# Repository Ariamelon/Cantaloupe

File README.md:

# Cantaloupe
~60% 60-key ZMK-compatible wireless split ergonomic keyboard.

## Disclaimer
This keyboard is licensed under CERN-OHL-S-2.0. The layout is based on the [Ergodash](https://github.com/omkbd/ErgoDash) layout with the inner-most keys removed and an improved thumb cluster. The layout was only used as a reference, nothing was copied and the board is a completely new design.

## Key Features
* Ergonomic split 30-key vertically staggered layout with thumb cluster, pinky stagger and arrow keys.
* [VIK](https://github.com/sadekbaroudi/vik) module support.
* On-board nRF52840 BLE 5.3 MCU.
* nPM1300 PMIC for power management.
* Battery shipping mode switch while allowing for charging when plugged in.
* 702050 700mAh battery with built-in NTC for temperature protection.
* SWD Tag-Connect header for debugging purposes.
* USB-C input with full ESD protection.
* MX, Kailh Choc V1/V2 and Gateron KS-27/KS-33 hotswap support.
* Gasket-mount case with adjustable tent (?).

## Changelog
* 22/10/2024: License updated to CERN-OHL-S-2.0.
* 16/10/2024: Cantaloupe V3.0 name changed to CantaloupeBT V1.0 ('BT-V1' branch). Key features updated. Design will be reworked in the coming days!
* 24/08/2023: Finished routing. Consolidated all libraries into [Ariamelon's Kicad Master Library](https://github.com/Ariamelon/Ariamelon-Kicad-Master-Library). Added PCM12 switch connected to nPM1300 GPIO. Rearranged components and rerouted. 
* 23/08/2023: Changed MCU to nRF52840. Added nPM1300 PMIC for power management. Replaced SSD1351 display with Nice!View. Added Kailh Choc V1/V2 and Gateron KS-27/KS-33 support. 
* 08/08/2023: Removed Ogen footprint, and future VIK support is planned. Rerouted board following latest Honeydew revision. WIP support for the USB2541 is added, but it's very tentative and not yet complete. Added CX70M-24P1 footprint.
* 25/03/2023: Routing complete. Footprint added for the [Ogen](https://github.com/Ariamelon/Ogen/), allowing for a trackball or trackpad to be used.
* 19/03/2023: Initial V3.0 version committed (still in progress). Board has been completely reworked (again) and will be another completely new design, based on the [Honeydew](https://github.com/Ariamelon/Honeydew/). Added CC BY 4.0 license.
* 30/05/2022: Changed XC6206P332MR-G to XC6220B331MR-G for more power output. Changed fuse to 1A. Fixed library links. Changed AO6802 back to two AO3400s. Moved reset circuit downwards and extra pin header upwards for better routing. Updated BOM.
* 28/05/2022: Added another 10u filtering cap. Rerouted power track. Changed pin assignments. Changed values of VBUS detect to use already existing values on the board.
* 26/05/2022: Fixed mistakes with bottom cases. Added piece which is meant to mate with the button, allowing the reset to be pressed without needing a screwdriver. Update to USB port name and footprint (no functional change). Updated pin assignments. Rerouted board.
* 24/05/2022: Changed the matrix diodes to dual MMBD4148ACC diodes. Swapped ROW1 and COL0 pins. Fixed minor issue with case models. Updated BOM. Added LCSC part names to all parts on schematic.
* 23/05/2022: Updated trackpad plate models. Fixed OLED silk. 
* 22/05/2022: Added footprints for SPI FRAM/EEPROM and flash memory. Added breakout header to expose some unused pins. Fixed 3D models for plate pot. Updated 3D model for the EC11. Changed the two AO3400s to a AO6802 dual NMOS. Replaced switch with a more durable version that's the same size while keeping the footprint compatible with the previous switch. Updated BOM.
* 21/05/2022: Revised schematic. Switched trackpad to SPI interface and moved header. Moved location of OLED screen and changed footprint. Changed indicator LED to a small RGB one, and added an RGB header. Moved USB ports and reset button. Much better revised cases. Slightly increased horizontal size to fully accommodate the Cirque TM35035. Added lots of 3D models for all the footprints. Removed V1 as that was no longer being updated.
* 15/05/2022: V2.1 version updates. Removed silkscreen jumper guides, pimoroni trackball header and plate for trackpad. Updated BOM.
* 14/05/2022: Added silkscreen jumper guides. Connected indicator LED to spare GPIO. Updated images. Added optional I2C resistors. New logo. New plate CAD files for potentiometer, trackball and trackpad options. Added header for Cirque trackpad. Cleaned up footprint library.
* 13/05/2022: Updated firmware. Added custom graphic to OLED display. Updated 3DP case and BOM. Removed CNC case. Fixed error with silkscreen. Added silkscreen jumper guides.
* 15/02/2022: Revised 3DP and CNC case designs.
* 13/02/2022: Added tentative designs for CNC and 3D printed cases. 
* 11/02/2022: Clean up of design. New images. Added gerbers and files for FR4 plates.
* 9/02/2022: Changed pin assignments so B2 isn't used. Added pull-up for RX pin and pull-down for B2 pin so the keyboard can properly load into the bootloader. Changed reset circuit so it actually works. Removed USB series resistors. Removed non-functional JTAG pins. Changed SRV05-04 to SRV0504. Thanks to sigprof and MasterSpoon from the QMK discord server for the help!
* 8/02/2022: Removed holes in middle of PCB. Added top and bottom plate DXF files, as well as a tentative STEP file for a CNC case. 
* 25/01/2022: Did some rerouting, increased clearances and via size.
* 21/01/2022: Changed CPU to STM32F401CCU6 (lets me steal them from Black Pill boards). Added plate and base gerber files. Changed BOM to reflect changes.
* 20/01/2022: Cleaned up read-me. Rearranged location of mounting holes and changed size of holes. Rerouted some traces. Cleaned up silkscreen. Added DXF files for plate and base. Changed images. Added BOM.
* 19/01/2022: New V2.0 version. On-board ARM STM32F303 processor, kailh hot-swap, ESD protection, 0.96" OLED, trackball and rotary encoder. 100% reversible design which means only a single board is needed for both sides. Plenty of design cues taken from the YAEMK. Pinky stagger added.
* 6/12/2021: Updated to V1.5. Added the option for OLED again. Removed Alps support. Improved switch footprints. Removed 2u support and moved rotary encoder positions. Deleted 61st and 62nd keyswitches - now has exactly 30 switches per side. Changed USB C interconnect back to TRRS and moved position.
* 1/10/2021: Added SMK support again (I'm indecisive).
* 20/07/2021: Updated to V1.4. Removed OLED support, as I don't actually care about OLED and haven't been using it with the previous prototype for a while.
* 17/05/2021: Fixed BOM and added proper OLED support.
* 2/12/2020: Changed orientation of 1u switches in thumb cluster. Updated plate to add 2u support.
* 1/12/2020: Changed OLED compatibility to 0.96" OLED. Removed Crenshaw compatibility. Removed large cutout in plate for pro micro and Crenshaw, added smaller cutout just showing screen of 0.96" OLED.
* 29/11/2020: Updated to V1.3. Added 2u switch locations in outer bottom corners and thumb cluster. Slightly increased size to allow for high-profile case options. Changed mounting holes on PCB to pass-through holes to allow for direct top and bottom plate mounting. Removed SMK switch support. Updated plate to add Alps compatibility.
* 14/11/2020: Changed USB C connector to normal from mid-mount.
* 11/11/2020: Updated to V1.2. Switch footprints changed to solder holes, compatible with MX, Alps and SMK switches. 5-way switch removed. Pro Micros flipped, facing downward, to reduce overall thickness of keyboard. Diode footprints changed to allow use of both TH and SMD (SOD-123(F) and glass DO-35) diodes.
* 7/11/2020: Fixed position of RHS screw hole and wiring of rotary encoder switch, added QMK firmware.
* 28/10/2020: Better photo, reorganized footprints, minor fixes to circuit.
* 25/10/2020: Added back 5-way switch. Removed SMK support. New renders.
* 24/10/2020: Updated to V1.1. Slightly increased stagger and different PCB shape based on the [Galia](https://github.com/Ariamelon/Galia), removed snap-away interconnect section of PCB, added ICSP header. Moved location of images folder.
* 28/09/2020: Added case files.
* 27/09/2020: Initial commit.

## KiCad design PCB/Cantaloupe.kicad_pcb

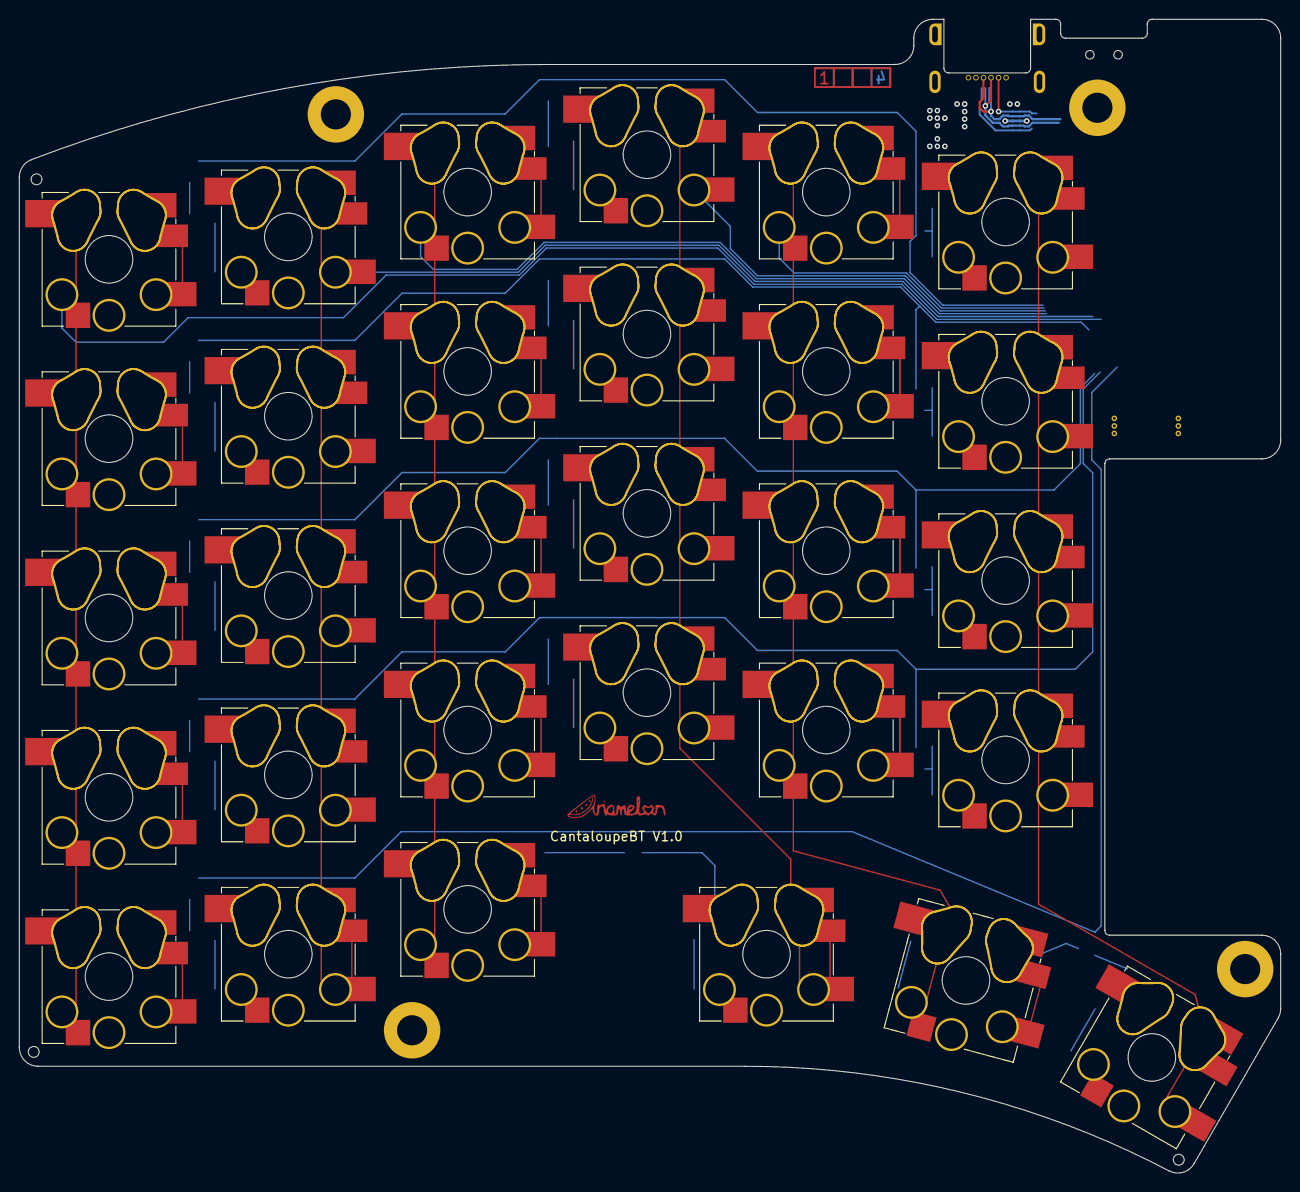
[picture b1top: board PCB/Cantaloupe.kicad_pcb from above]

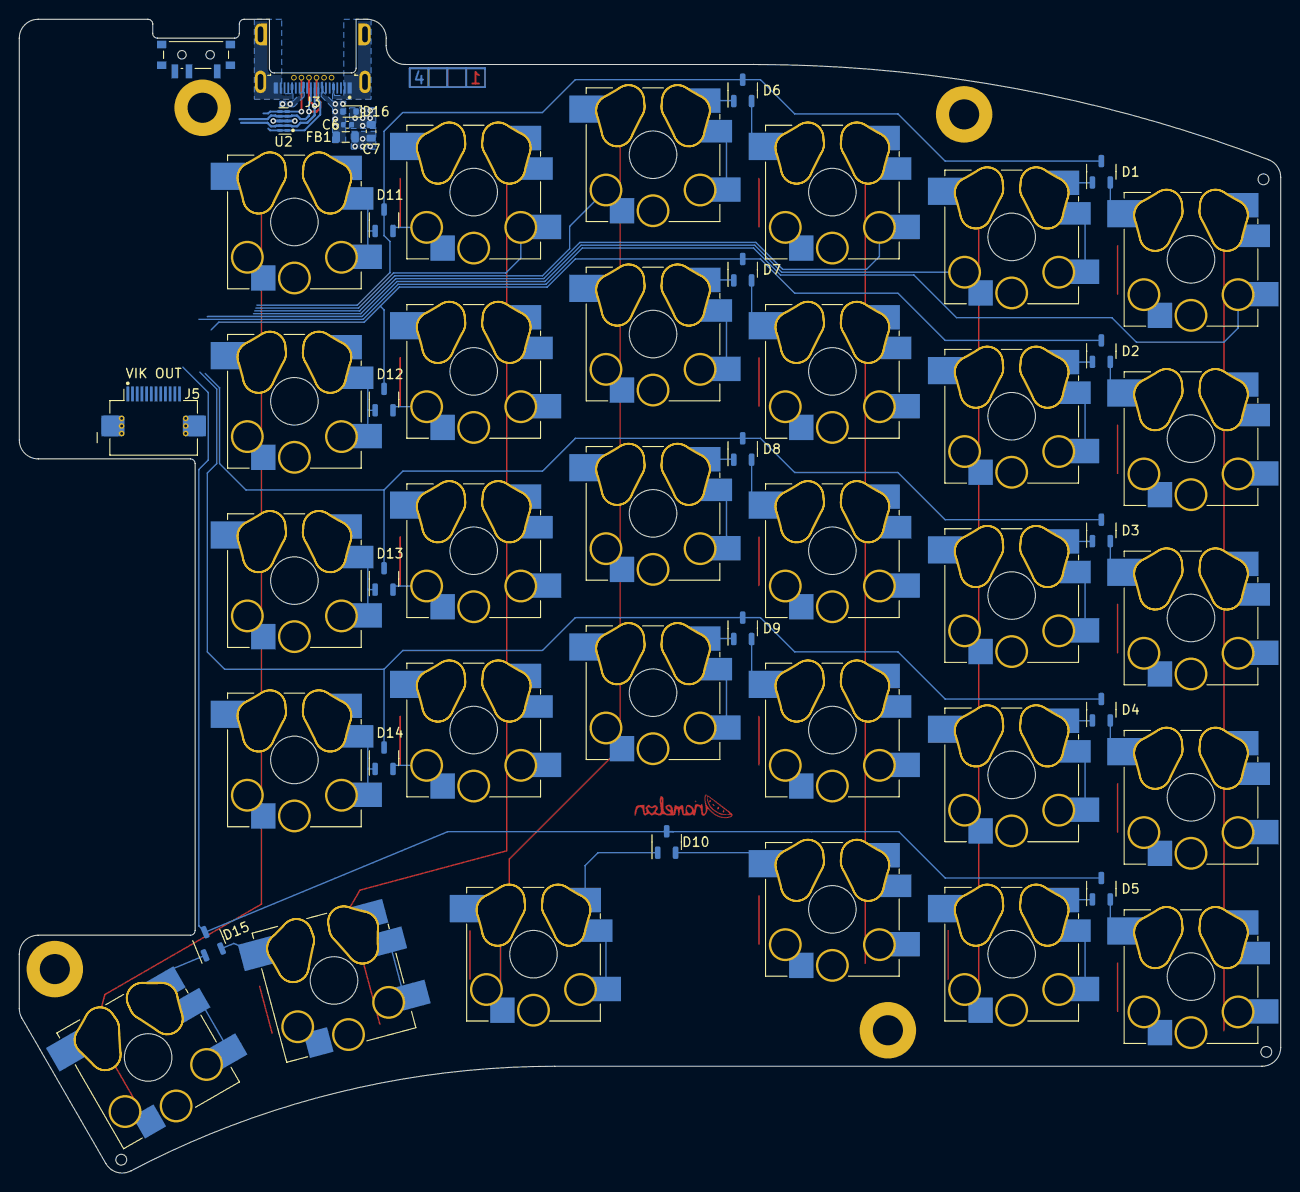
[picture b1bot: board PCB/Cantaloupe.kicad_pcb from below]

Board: 4 copper layers, 134.0 x 122.6 mm, 61 parts (56 on the bottom side), 48 nets.

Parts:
A1: Ariamelon Logo; Ariamelon_Logo_Small_CU
C6: 10n; C_0402_1005Metric
C7: 1u; C_0603_1608Metric
D1, D2, D3, D4, D5, D6, D7, D8, D9, D10, D11, D12, D13, D14, D15: BAV70; SOT-23-3
D16: 5V; D_SOD-523
FB1: 60R; L_0805_2012Metric
H1, H2, H3: Tooling Hole; MountingHole_JLC-Tooling
H4, H5, H6, H7: M3; MountingHole_3.2mm_M3_Pad
J3: USB_C_Receptacle; Hirose_CX70M-24P1
J5: VIK Keyboard; VIK_Keyboard_Horizontal
SW1, SW2, SW3, SW4, SW5, SW6, SW7, SW8, SW9, SW10, SW11, SW12, SW13, SW14, SW15, SW16, SW17, SW18, SW19, SW20, SW21, SW22, SW23, SW24, SW25, SW26, SW27, SW28, SW29, SW30: CPG151101S11; SW_MX-Choc-KS27_1U_Hotswap_Flippable
SW33: SW_SPDT; SW_CK_SPDT_PCM12
U2: TPD4E05U06; USON-10_2.5x1.0mm_P0.5mm

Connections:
/IO/USB_D+: J3.A6 (D+), J3.B6 (D+), U2.2 (IO2), U2.9 (NC)
/IO/USB_D-: J3.A7 (D-), J3.B7 (D-), U2.4 (IO3), U2.7 (NC)
/MCU/COL0: SW1.1 (A), SW2.1 (A), SW3.1 (A), SW4.1 (A), SW5.1 (A)
/MCU/COL1: SW6.2 (B), SW7.2 (B), SW8.2 (B), SW9.2 (B), SW10.2 (B)
/MCU/COL2: SW11.1 (A), SW12.1 (A), SW13.1 (A), SW14.1 (A), SW15.1 (A)
/MCU/COL3: SW16.2 (B), SW17.2 (B), SW18.2 (B), SW19.2 (B), SW20.2 (B)
/MCU/COL4: SW21.1 (A), SW22.1 (A), SW23.1 (A), SW24.1 (A), SW25.1 (A)
/MCU/COL5: SW26.2 (B), SW27.2 (B), SW28.2 (B), SW29.2 (B), SW30.2 (B)
/MCU/ROW0: D1.3 (K), D6.3 (K), D11.3 (K)
/MCU/ROW1: D2.3 (K), D7.3 (K), D12.3 (K)
/MCU/ROW2: D3.3 (K), D8.3 (K), D13.3 (K)
/MCU/ROW3: D4.3 (K), D9.3 (K), D14.3 (K)
/MCU/ROW4: D5.3 (K), D10.3 (K), D15.3 (K)
CC1: J3.A5 (CC1), U2.1 (IO1), U2.10 (NC)
CC2: J3.B5 (CC2), U2.5 (IO4), U2.6 (NC)
GND: C6.1, C7.2, D16.1 (K), H7.1, J3.A1 (GND), J3.A12 (GND), J3.B1 (GND), J3.B12 (GND), J3.S1 (SHIELD), J5.2 (GND), J5.MP, U2.3 (GND), U2.8 (GND)
unnamed: D1.1 (A), SW6.1 (A)
unnamed: D1.2 (A), SW1.2 (B)
unnamed: D2.1 (A), SW7.1 (A)
unnamed: D2.2 (A), SW2.2 (B)
unnamed: D3.1 (A), SW8.1 (A)
unnamed: D3.2 (A), SW3.2 (B)
unnamed: D4.1 (A), SW9.1 (A)
unnamed: D4.2 (A), SW4.2 (B)
unnamed: D5.1 (A), SW10.1 (A)
unnamed: D5.2 (A), SW5.2 (B)
unnamed: D6.1 (A), SW16.1 (A)
unnamed: D6.2 (A), SW11.2 (B)
unnamed: D7.1 (A), SW17.1 (A)
unnamed: D7.2 (A), SW12.2 (B)
unnamed: D8.1 (A), SW18.1 (A)
unnamed: D8.2 (A), SW13.2 (B)
unnamed: D9.1 (A), SW19.1 (A)
unnamed: D9.2 (A), SW14.2 (B)
unnamed: D10.1 (A), SW20.1 (A)
unnamed: D10.2 (A), SW15.2 (B)
unnamed: D11.1 (A), SW26.1 (A)
unnamed: D11.2 (A), SW21.2 (B)
unnamed: D12.1 (A), SW27.1 (A)
unnamed: D12.2 (A), SW22.2 (B)
unnamed: D13.1 (A), SW28.1 (A)
unnamed: D13.2 (A), SW23.2 (B)
unnamed: D14.1 (A), SW29.1 (A)
unnamed: D14.2 (A), SW24.2 (B)
unnamed: D15.1 (A), SW30.1 (A)
unnamed: D15.2 (A), SW25.2 (B)
VBUS: C7.1, FB1.1
VBUS_RAW: C6.2, D16.2 (A), FB1.2, J3.A4 (VBUS), J3.A9 (VBUS), J3.B4 (VBUS), J3.B9 (VBUS)

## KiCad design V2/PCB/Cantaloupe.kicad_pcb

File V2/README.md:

# Cantaloupe
On-board MCU version.

## Key Features
* On-board ARM STM32F401CCU6 processor.
* USB-C input and split connect ports with full ESD protection.
* SWD breakout header for an alternate means of programming the board.

## Changelog
* 15/2/2022: V2.1 version. Removed silkscreen jumper guides, pimoroni trackball header and plate for trackpad. Updated BOM.
* 14/5/2022: Added silkscreen jumper guides. Connected indicator LED to spare GPIO. Updated images. Added optional I2C resistors. New logo. New plate CAD files for potentiometer, trackball and trackpad options. Added header for Cirque trackpad. Cleaned up footprint library.
* 13/5/2022: Finalized firmware. Added custom graphic to OLED display. Updated 3DP case and BOM. Removed CNC case. Fixed error with silkscreen. Added silkscreen jumper guides.
* 15/2/2022: Revised 3DP and CNC case designs.
* 13/2/2022: Added tentative designs for CNC and 3D printed cases. 
* 11/2/2022: Clean up of design. New images. Added gerbers and files for FR4 plates.
* 9/2/2022: Changed pin assignments so B2 isn't used. Added pull-up for RX pin and pull-down for B2 pin so the keyboard can properly load into the bootloader. Changed reset circuit so it actually works. Removed USB series resistors. Removed non-functional JTAG pins. Changed SRV05-04 to SRV0504. Thanks to sigprof and MasterSpoon from the QMK discord server for the help!
* 8/2/2022: Removed holes in middle of PCB. Added top and bottom plate DXF files, as well as a tentative STEP file for a CNC case. 
* 25/1/2022: Did some rerouting, increased clearances and via size.
* 21/1/2022: Changed CPU to STM32F4x1CxUx (lets me steal them from Black Pill boards). Added plate and base gerber files. Changed BOM to reflect changes.
* 20/1/2022: Cleaned up read-me. Rearranged location of mounting holes and changed size of holes. Rerouted some traces. Cleaned up silkscreen. Added DXF files for plate and base. Changed images. Added BOM.
* 19/1/2022: New V2.0 version. On-board ARM STM32F303 processor, kailh hot-swap, ESD protection, 0.96" OLED, trackball and rotary encoder. 100% reversible design which means only a single board is needed for both sides. Plenty of design cues taken from the YAEMK. Pinky stagger added.

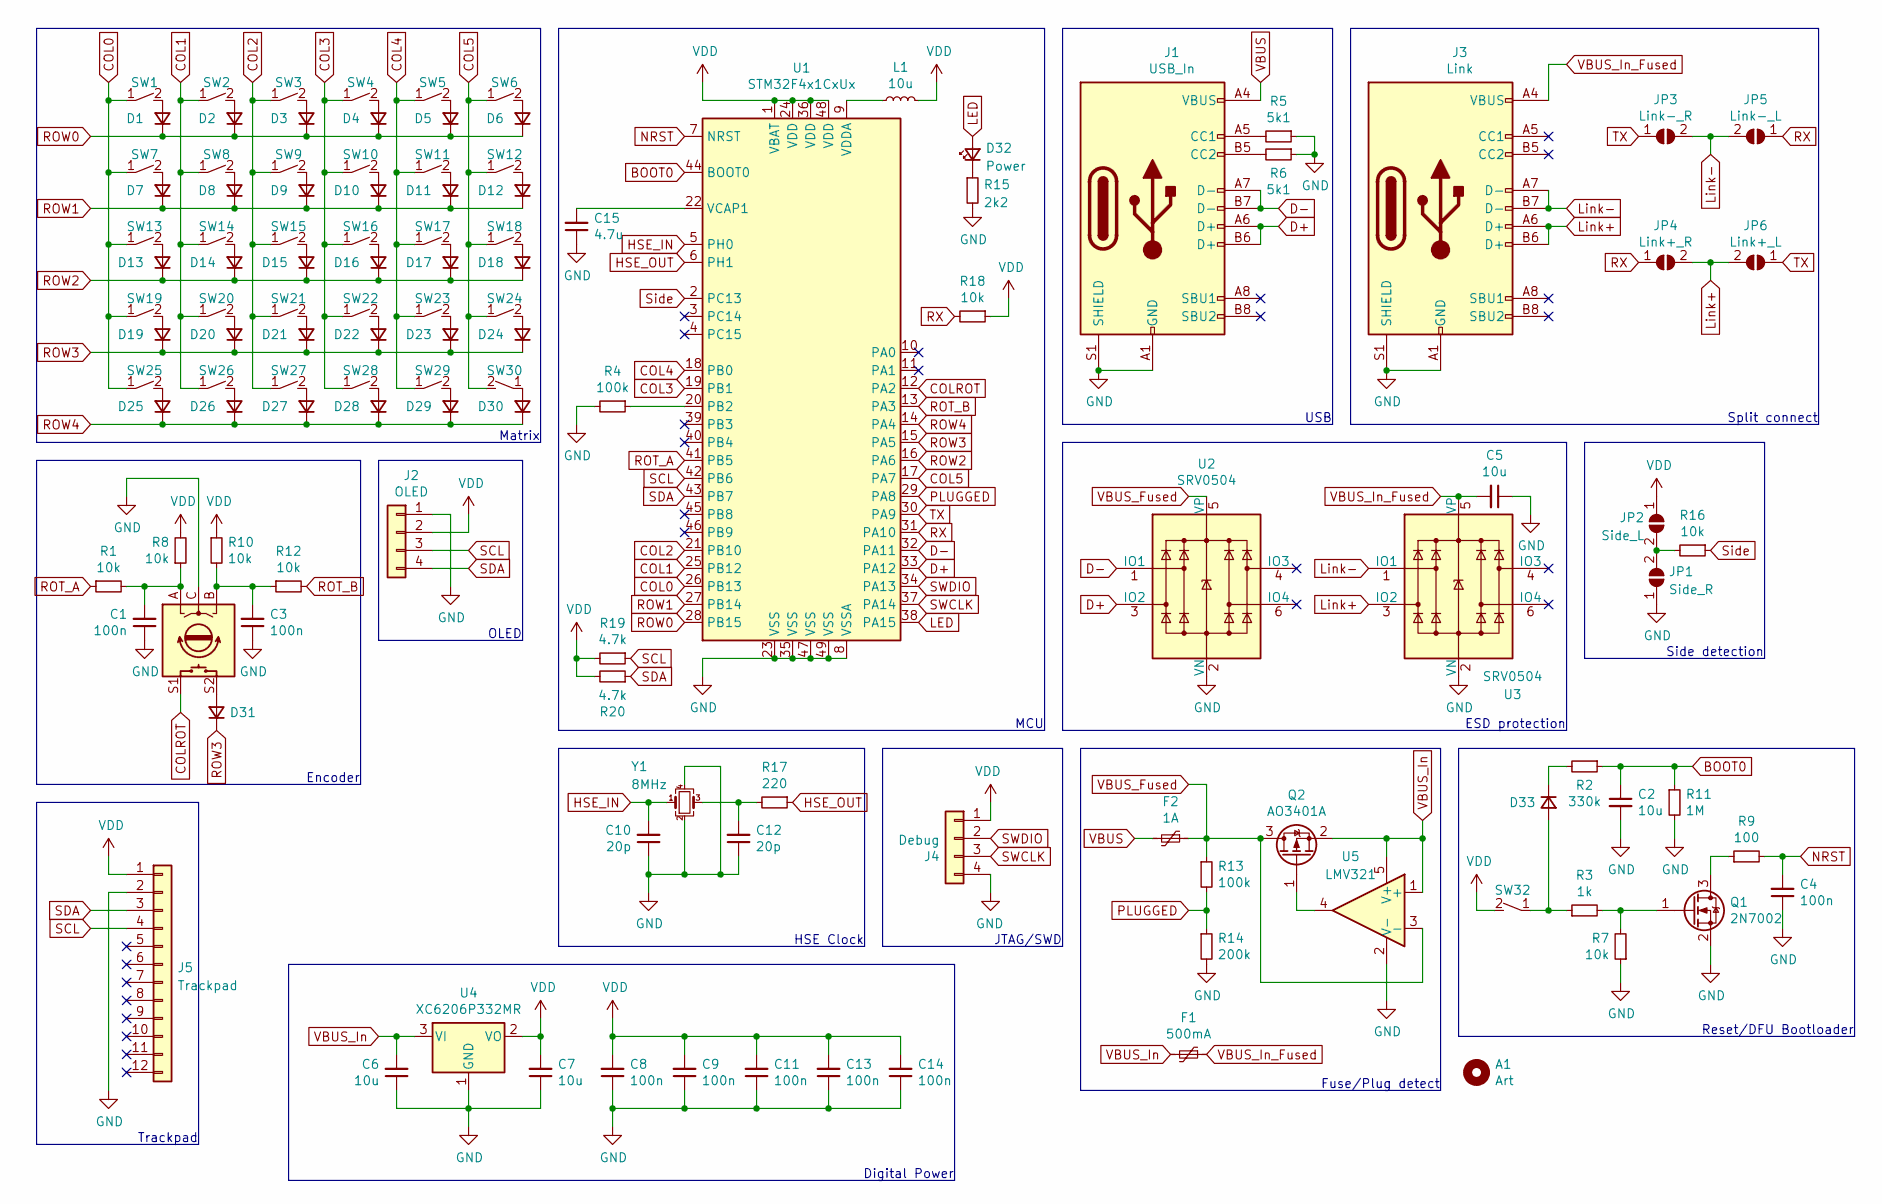
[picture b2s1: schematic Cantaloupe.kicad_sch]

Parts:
A1: Art; Ariamelon_Logo_x2
C1, C3, C4, C8, C9, C11, C13, C14: 100n; C_0603_1608Metric
C2, C5, C6, C7: 10u; C_0603_1608Metric
C10, C12: 20p; C_0603_1608Metric
C15: 4.7u; C_0603_1608Metric
D1, D2, D3, D4, D5, D6, D7, D8, D9, D10, D11, D12, D13, D14, D15, D16, D17, D18, D19, D20, D21, D22, D23, D24, D25, D26, D27, D28, D29, D30, D31, D33: D; D_SOD-123
D32: Power; LED_0603_1608Metric_Flippable
F1: 500mA; Fuse_1206_3216Metric
F2: 1A; Fuse_1206_3216Metric
J1: USB_In; USB-C-C168688
J2: OLED; OLED_0.96_SSD1306_128x64_Flippable
J3: Link; USB-C-C168688
J4: Debug; Debug_JTAG_SWD
J5: Trackpad; Hirose_FH12-12S-0.5SH_1x12-1MP_P0.50mm_Horizontal
JP1: Side_R; SolderJumper-2_P1.3mm_Open_Pad1.0x1.5mm
JP2: Side_L; SolderJumper-2_P1.3mm_Open_Pad1.0x1.5mm
JP3: Link-_R; SolderJumper-2_P1.3mm_Open_Pad1.0x1.5mm
JP4: Link+_R; SolderJumper-2_P1.3mm_Open_Pad1.0x1.5mm
JP5: Link-_L; SolderJumper-2_P1.3mm_Open_Pad1.0x1.5mm
JP6: Link+_L; SolderJumper-2_P1.3mm_Open_Pad1.0x1.5mm
L1: 10u; L_0603_1608Metric
Q1: 2N7002; SOT-23
Q2: AO3401A; SOT-23
R1, R7, R8, R10, R12, R16, R18: 10k; R_0603_1608Metric
R2: 330k; R_0603_1608Metric
R3: 1k; R_0603_1608Metric
R4, R13: 100k; R_0603_1608Metric
R5, R6: 5k1; R_0603_1608Metric
R9: 100; R_0603_1608Metric
R11: 1M; R_0603_1608Metric
R14: 200k; R_0603_1608Metric
R15: 2k2; R_0603_1608Metric
R17: 220; R_0603_1608Metric
R19, R20: 4.7k; R_0603_1608Metric
SW1, SW2, SW3, SW4, SW5, SW6, SW7, SW8, SW9, SW10, SW11, SW12, SW13, SW14, SW15, SW16, SW17, SW18, SW19, SW20, SW21, SW22, SW23, SW24, SW25, SW26, SW27, SW28, SW29, SW30: MX; MXOnly-1U-Hotswap-Dual
SW31: Encoder; EC11_Flippable
SW32: MX; Switch_TS24CA_Flippable
U1: STM32F4x1CxUx; QFN-48-1EP_7x7mm_P0.5mm_EP5.6x5.6mm
U2, U3: SRV0504; SOT-23-6
U4: XC6206P332MR; SOT-23
U5: LMV321; SOT-23-5
Y1: 8MHz; Crystal_SMD_3225-4Pin_3.2x2.5mm

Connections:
BOOT0: C2.1, R2.1, R11.1, U1.44 (BOOT0)
COL0: SW1.1 (A), SW7.1 (A), SW13.1 (A), SW19.1 (A), SW25.1 (A), U1.26 (PB13)
COL1: SW2.1 (A), SW8.1 (A), SW14.1 (A), SW20.1 (A), SW26.1 (A), U1.25 (PB12)
COL2: SW3.1 (A), SW9.1 (A), SW15.1 (A), SW21.1 (A), SW27.1 (A), U1.21 (PB10)
COL3: SW4.1 (A), SW10.1 (A), SW16.1 (A), SW22.1 (A), SW28.1 (A), U1.19 (PB1)
COL4: SW5.1 (A), SW11.1 (A), SW17.1 (A), SW23.1 (A), SW29.1 (A), U1.18 (PB0)
COL5: SW6.1 (A), SW12.1 (A), SW18.1 (A), SW24.1 (A), SW30.2 (B), U1.17 (PA7)
COLROT: SW31.S1, U1.12 (PA2)
D+: J1.A6 (D+), J1.B6 (D+), U1.33 (PA12), U2.3 (IO2)
D-: J1.A7 (D-), J1.B7 (D-), U1.32 (PA11), U2.1 (IO1)
GND: C1.1, C2.2, C3.1, C4.1, C5.1, C6.1, C7.1, C8.1, C9.1, C10.1, C11.1, C12.1, C13.1, C14.1, C15.1, J1.A1 (GND), J1.A12 (GND), J1.B1 (GND), J1.B12 (GND), J1.S1 (SHIELD), J2.1, J3.A1 (GND), J3.A12 (GND), J3.B1 (GND), J3.B12 (GND), J3.S1 (SHIELD), J4.4, J5.2, JP1.1 (A), Q1.2 (S), R4.2, R5.1, R6.1, R7.1, R11.2, R14.2, R15.2, SW31.C, U1.8 (VSSA), U1.23 (VSS), U1.35 (VSS), U1.47 (VSS), U1.49 (VSS), U2.2 (VN), U3.2 (VN), U4.1 (GND), U5.2 (V-), Y1.2, Y1.4
HSE_IN: C10.2, U1.5 (PH0), Y1.1
HSE_OUT: R17.1, U1.6 (PH1)
LED: D32.2 (A), U1.38 (PA15)
Link+: J3.A6 (D+), J3.B6 (D+), JP4.2 (B), JP6.2 (B), U3.3 (IO2)
Link-: J3.A7 (D-), J3.B7 (D-), JP3.2 (B), JP5.2 (B), U3.1 (IO1)
NRST: C4.2, R9.2, U1.7 (NRST)
unnamed: C1.2, R1.2, R8.1, SW31.A
unnamed: C3.2, R10.2, R12.1, SW31.B
unnamed: C12.2, R17.2, Y1.3
unnamed: C15.2, U1.22 (VCAP1)
unnamed: D1.2 (A), SW1.2 (B)
unnamed: D2.2 (A), SW2.2 (B)
unnamed: D3.2 (A), SW3.2 (B)
unnamed: D4.2 (A), SW4.2 (B)
unnamed: D5.2 (A), SW5.2 (B)
unnamed: D6.2 (A), SW6.2 (B)
unnamed: D7.2 (A), SW7.2 (B)
unnamed: D8.2 (A), SW8.2 (B)
unnamed: D9.2 (A), SW9.2 (B)
unnamed: D10.2 (A), SW10.2 (B)
unnamed: D11.2 (A), SW11.2 (B)
unnamed: D12.2 (A), SW12.2 (B)
unnamed: D13.2 (A), SW13.2 (B)
unnamed: D14.2 (A), SW14.2 (B)
unnamed: D15.2 (A), SW15.2 (B)
unnamed: D16.2 (A), SW16.2 (B)
unnamed: D17.2 (A), SW17.2 (B)
unnamed: D18.2 (A), SW18.2 (B)
unnamed: D19.2 (A), SW19.2 (B)
unnamed: D20.2 (A), SW20.2 (B)
unnamed: D21.2 (A), SW21.2 (B)
unnamed: D22.2 (A), SW22.2 (B)
unnamed: D23.2 (A), SW23.2 (B)
unnamed: D24.2 (A), SW24.2 (B)
unnamed: D25.2 (A), SW25.2 (B)
unnamed: D26.2 (A), SW26.2 (B)
unnamed: D27.2 (A), SW27.2 (B)
unnamed: D28.2 (A), SW28.2 (B)
unnamed: D29.2 (A), SW29.2 (B)
unnamed: D30.2 (A), SW30.1 (A)
unnamed: D31.2 (A), SW31.S2
unnamed: D32.1 (K), R15.1
unnamed: D33.1 (K), R2.2
unnamed: D33.2 (A), R3.1, SW32.1 (A)
unnamed: J1.A5 (CC1), R5.2
unnamed: J1.B5 (CC2), R6.2
unnamed: JP1.2 (B), JP2.2 (B), R16.2
unnamed: L1.1, U1.9 (VDDA)
unnamed: Q1.1 (G), R3.2, R7.2
unnamed: Q1.3 (D), R9.1
unnamed: Q2.1 (G), U5.4
unnamed: R4.1, U1.20 (PB2)
PLUGGED: R13.2, R14.1, U1.29 (PA8)
ROT_A: R1.1, U1.41 (PB5)
ROT_B: R12.2, U1.13 (PA3)
ROW0: D1.1 (K), D2.1 (K), D3.1 (K), D4.1 (K), D5.1 (K), D6.1 (K), U1.28 (PB15)
ROW1: D7.1 (K), D8.1 (K), D9.1 (K), D10.1 (K), D11.1 (K), D12.1 (K), U1.27 (PB14)
ROW2: D13.1 (K), D14.1 (K), D15.1 (K), D16.1 (K), D17.1 (K), D18.1 (K), U1.16 (PA6)
ROW3: D19.1 (K), D20.1 (K), D21.1 (K), D22.1 (K), D23.1 (K), D24.1 (K), D31.1 (K), U1.15 (PA5)
ROW4: D25.1 (K), D26.1 (K), D27.1 (K), D28.1 (K), D29.1 (K), D30.1 (K), U1.14 (PA4)
RX: JP4.1 (A), JP5.1 (A), R18.2, U1.31 (PA10)
SCL: J2.3, J5.4, R19.1, U1.42 (PB6)
SDA: J2.4, J5.3, R20.1, U1.43 (PB7)
SWCLK: J4.3, U1.37 (PA14)
SWDIO: J4.2, U1.34 (PA13)
Side: R16.1, U1.2 (PC13)
TX: JP3.1 (A), JP6.1 (A), U1.30 (PA9)
VBUS: F2.2, J1.A4 (VBUS), J1.A9 (VBUS), J1.B4 (VBUS), J1.B9 (VBUS)
VBUS_Fused: F2.1, Q2.3 (D), R13.1, U2.5 (VP), U5.3 (-)
VBUS_In: C6.2, F1.2, Q2.2 (S), U4.3 (VI), U5.1 (+), U5.5 (V+)
VBUS_In_Fused: C5.2, F1.1, J3.A4 (VBUS), J3.A9 (VBUS), J3.B4 (VBUS), J3.B9 (VBUS), U3.5 (VP)
VDD: C7.2, C8.2, C9.2, C11.2, C13.2, C14.2, J2.2, J4.1, J5.1, JP2.1 (A), L1.2, R8.2, R10.1, R18.1, R19.2, R20.2, SW32.2 (B), U1.1 (VBAT), U1.24 (VDD), U1.36 (VDD), U1.48 (VDD), U4.2 (VO)

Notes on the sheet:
HSE Clock
USB
Encoder
Trackpad
Matrix
Side detection
JTAG/SWD
Digital Power
Fuse/Plug detect
ESD protection
OLED
MCU
Reset/DFU Bootloader
Split connect

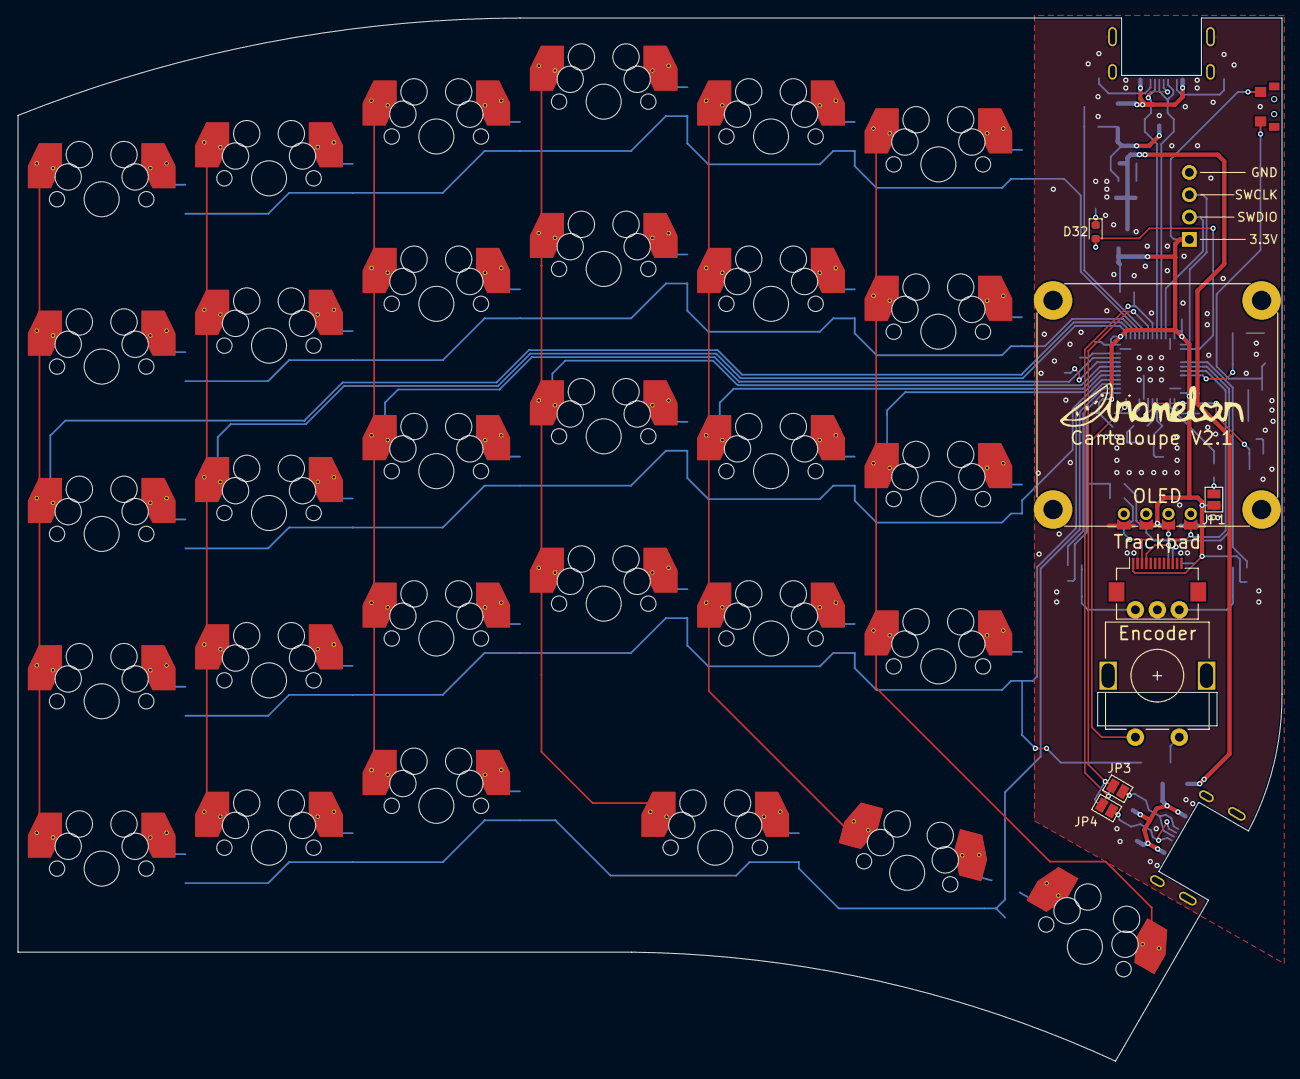
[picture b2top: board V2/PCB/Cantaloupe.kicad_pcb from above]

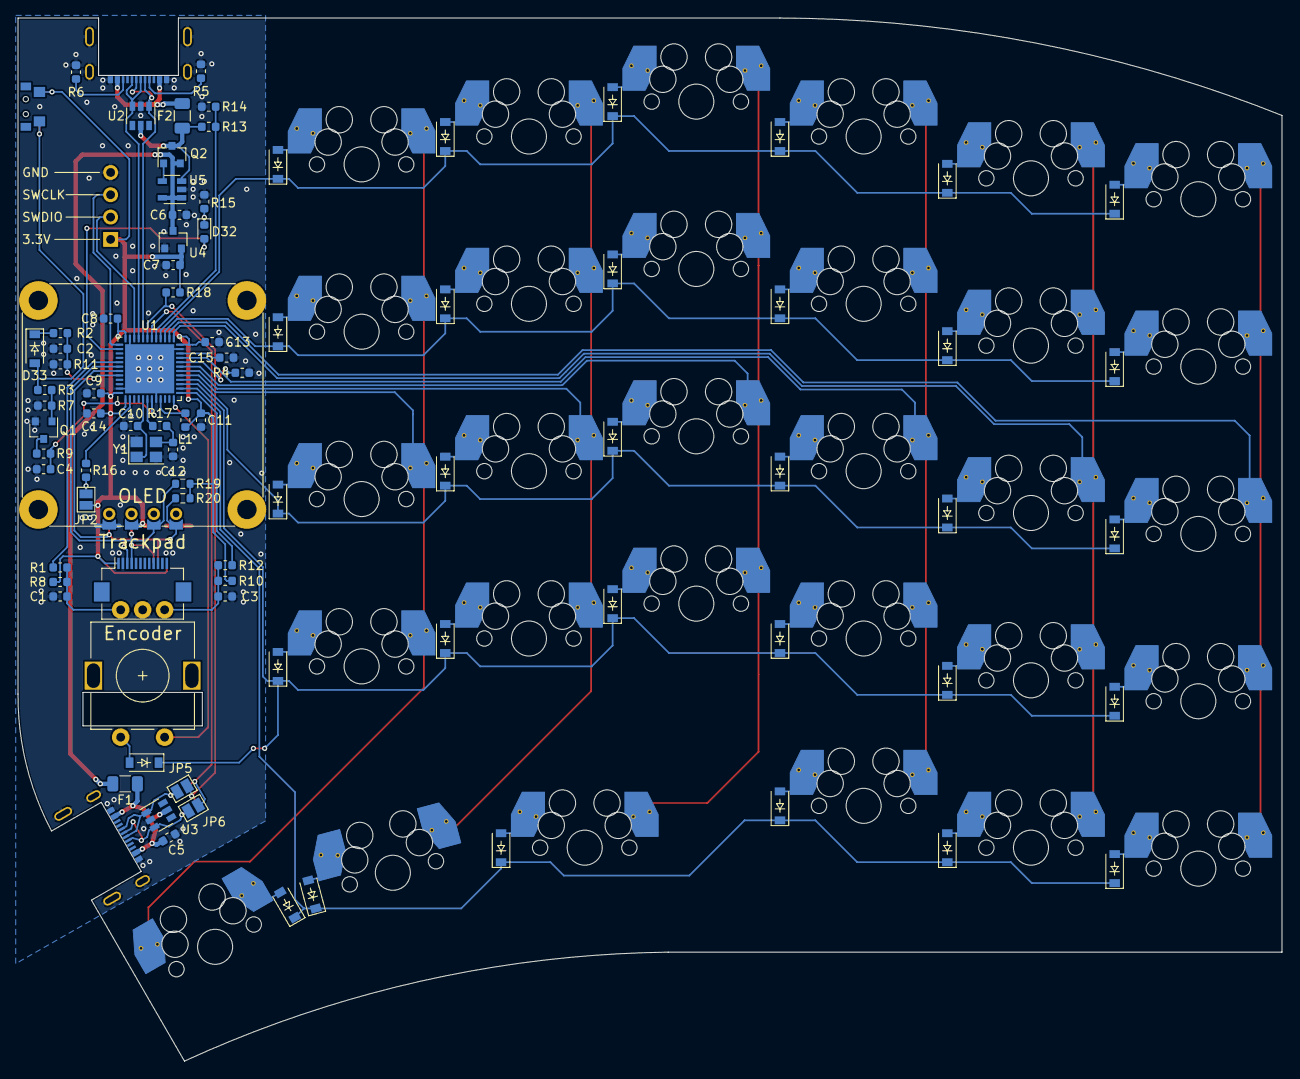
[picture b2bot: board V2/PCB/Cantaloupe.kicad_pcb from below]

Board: 2 copper layers, 143.9 x 118.7 mm, 123 parts (85 on the bottom side), 83 nets.

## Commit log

2020-09-27 Cantaloupe V1
    Added.
2020-09-27 Renamed folder
2020-09-27 Added link to the Crenshaw
2020-09-28 Proper case files and gerbers
    Added an STL file for a rudimentary 3D-printed case for the Cantaloupe as well as DXF and Gerber files for a plate.
2020-09-28 Added BOM
2020-09-28 Interconnect changed to C-168688
    Changed interconnect footprint to USB C-168688 due to lack of widespread availability of previous part.
2020-09-29 Grammar fix
2020-09-30 Update LICENSE
2020-09-30 Fixed silk
2020-10-01 Uploaded image and updated readme with it
2020-10-01 Oops
2020-10-01 Added back render
2020-10-24 Updated to V1.1
2020-10-24 Increased gap between halves
2020-10-24 Added photo
2020-10-27 Better photo, reorganized footprints, minor fixes to circuit
2020-10-29 Minor fix to position of RHS OLED
2020-10-31 Fixed minor silk error
2020-11-06 Fixed position of RHS screw hole and wiring of rotary encoder switch, added QMK firmware.
2020-11-10 Updated to V1.2
2020-11-13 Changed USB C connector to normal from mid-mount
2020-11-14 Added alps-compatible fr4 plate and cnc alu case STEP files
2020-11-20 Updated image
2020-11-28 Updated to V1.3.
2020-11-29 Updated position of diode
2020-11-30 Changed OLED support to 0.96" OLED
2020-12-02 Changed orientation of 1u switches in thumb cluster. Updated plate to add 2u support.
2021-05-08 Updated BOM
2021-05-16 Added proper OLED support.
2021-07-20 Updated to V1.4.
2021-07-20 Fixed PCB image
2021-10-01 Added SMK support
2021-12-06 Updated to V1.5.
    Added the option for OLED again. Removed Alps support. Improved switch footprints. Removed 2u support and moved rotary encoder positions. Deleted 61st and 62nd keyswitches - now has exactly 30 switch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
2022-01-19 New ARM variant (experimental WIP)
2022-01-20 20/1/2022 update
    Cleaned up read-me. Rearranged location of mounting holes and changed size of holes. Rerouted some traces. Cleaned up silkscreen. Added DXF files for plate and base. Changed images. Added BOM.
2022-01-21 STM32F4x0 version
2022-01-21 Added case gerbers
2022-01-21 Updated images and readme
2022-01-25 Did some rerouting, increased clearances and via size, updated footprint master
2022-01-25 Added V1.6
    V1.6 is the same as V2.0 but with a pro micro slot instead of the on-board ARM MCU. Separated V1.6 and V2.0 into specific folders. Added version-specific readme and images.
2022-02-08 New plate files, removed internal holes from PCB
2022-02-08 Fixed plate DXF files, added tentative .STEP file for a CNC case
2022-02-09 Fixed issues with PCB
    Changed pin assignments so B2 isn't used. Added pull-up for RX pin and pull-down for B2 pin so it can properly load into the bootloader.
2022-02-10 Fixed many issues with the board
    Changed pin assignments so B2 isn't used. Added pull-up for RX pin and pull-down for B2 pin so the keyboard can properly load into the bootloader. Changed reset circuit so it actually works. Removed 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
2022-02-10 Removed PCB mounting holes. Slightly changed position of reset switch.
2022-02-10 Rearranged schematic
2022-02-11 Clean up of design. Added gerbers and files for FR4 plates.
2022-02-11 Fixed jumper side
2022-02-13 Added tentative designs for CNC and 3D printed cases
2022-02-15 Revised 3DP and CNC case designs
2022-02-18 Added 3D files for top plate
2022-05-13 Finalized firmware. Added custom graphic to OLED display. Updated 3DP case and BOM. Fixed error with silkscreen.
2022-05-14 Update README.mdAdded silkscreen jumper guides. Connected indicator LED to spare GPIO. Updated images.
2022-05-14 Tentative V2.1 update
2022-05-14 Revert "Tentative V2.1 update"
    This reverts commit 42b4223a0f1e602d13e2d92696f419f95c71691f.
2022-05-14 Update to PCB and case files, added cirque header, clean up of library
    Added silkscreen jumper guides. Connected indicator LED to spare GPIO. Updated images. Added optional I2C resistors. New logo. New plate CAD files for potentiometer, trackball and trackpad options. A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
2022-05-21 Complete update to V2.1
2022-05-22 Further refinements to V2.1
2022-05-23 Updated trackpad plate models. Fixed OLED silk.
2022-05-26 Updates
    Update README.md. Added silkscreen jumper guides. Connected indicator LED to spare GPIO. Updated images.
2022-05-26 Further updates to V2.1
    Fixed mistakes with bottom cases. Added piece which is meant to mate with the button, allowing the reset to be pressed without needing a screwdriver. Update to USB port name and footprint (no functio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
2022-05-28 Added another 10u filtering cap. Rerouted power track. Changed pin assignments. Changed values of VBUS detect to use already existing values on the board.
2022-05-31 30/5/2022 changes
    Changed XC6206P332MR-G to XC6220B331MR-G for more power output. Changed fuse to 1A. Fixed library links. Changed AO6802 back to two AO3400s. Moved reset circuit downwards and extra pin header upwards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
2022-06-07 Better routing
2022-06-13 Updated case mounting
2023-03-20 INCOMPLETE V3.0 Initial Update
2023-03-21 More routing
2023-03-25 Routing done. Ogen footprint added.
2023-08-08 08/08/2023 update
    Removed Ogen footprint, and future VIK support is planned. Rerouted board following latest Honeydew revision. WIP support for the USB2541 is added, but it's very tentative and not yet complete. Added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
2023-08-24 23/08/2023 update
    Changed MCU to nRF52840. Added nPM1300 PMIC for power management. Replaced SSD1351 display with Nice!View. Added Kailh Choc V1/V2 and Gateron KS-27/KS-33 support.
2023-08-24 24/08/2023 update
    Finished routing. Consolidated all libraries into Ariamelon's Kicad Master Library. Added PCM12 switch connected to nPM1300 GPIO. Rearranged components and rerouted.
2024-10-16 Cantaloupe V3.0 name changed to CantaloupeBT V1.0 ('BT-V1' branch). Key features updated. Design will be reworked in the coming days!
2024-10-22 License updated to CERN-OHL-S-2.0.

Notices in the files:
PCB/Cantaloupe.kicad_pcb:
Licensed under CC BY 4.0.
